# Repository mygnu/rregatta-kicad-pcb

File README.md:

# rregatta-kicad-pcb

Full tutorial at [Building a sailing starter board with Rust (RTIC)](https://gill.net.in/posts/stm32-pcb-sailing-and-rust/)

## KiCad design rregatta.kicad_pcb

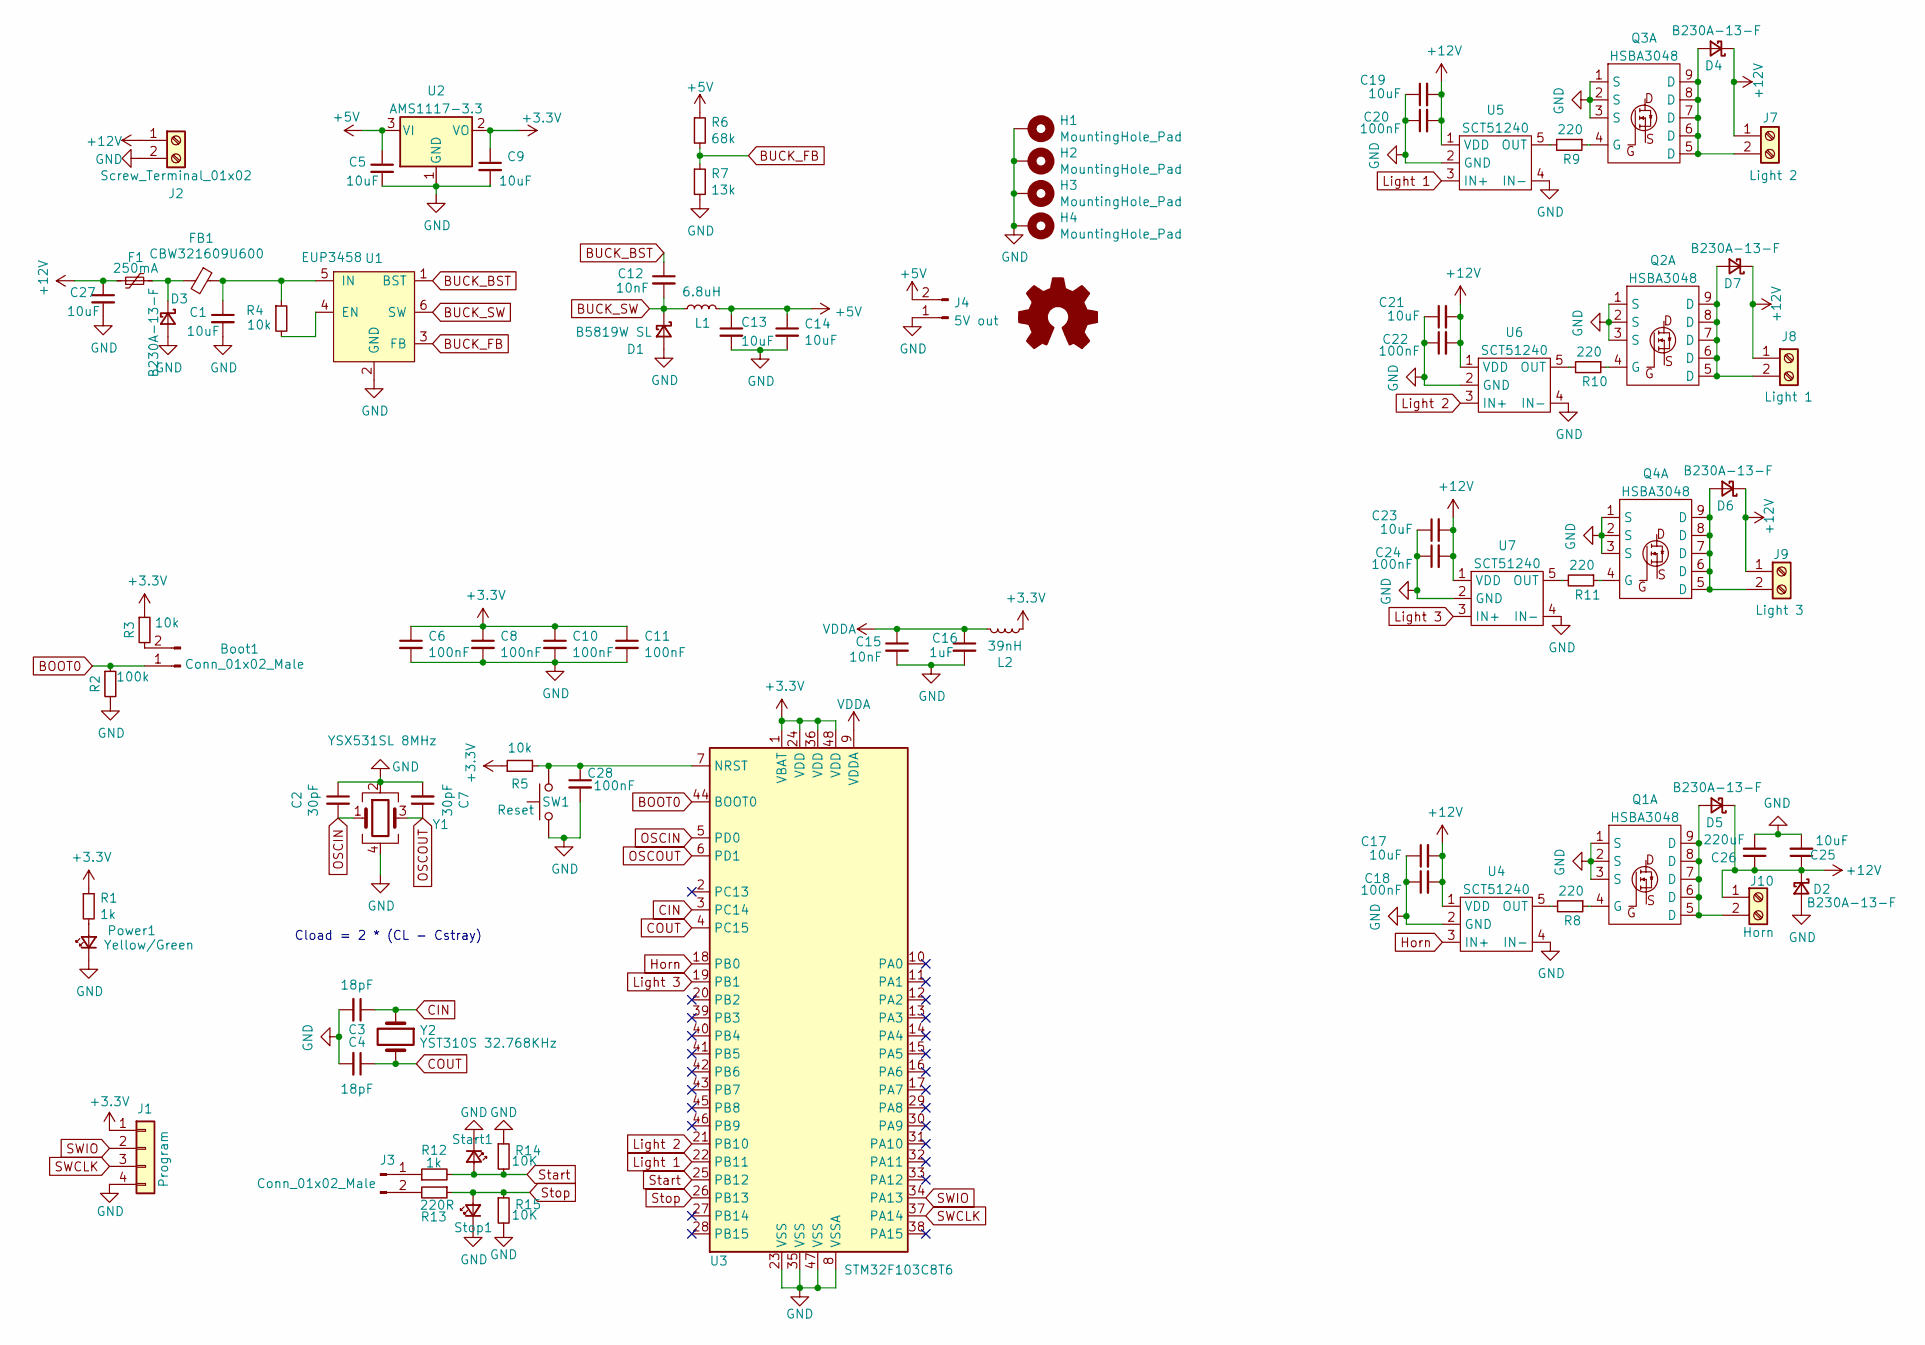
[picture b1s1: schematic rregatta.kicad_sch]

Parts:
Boot1: Conn_01x02_Male; PinHeader_1x02_P2.54mm_Vertical
C1, C5, C9, C13, C14, C17, C19, C21, C23, C25, C27: 10uF; C_0603_1608Metric_Pad1.08x0.95mm_HandSolder
C2, C7: 30pF; C_0603_1608Metric_Pad1.08x0.95mm_HandSolder
C3, C4: 18pF; C_0603_1608Metric_Pad1.08x0.95mm_HandSolder
C6, C8, C10, C11, C18, C20, C22, C24, C28: 100nF; C_0603_1608Metric_Pad1.08x0.95mm_HandSolder
C12, C15: 10nF; C_0603_1608Metric_Pad1.08x0.95mm_HandSolder
C16: 1uF; C_0603_1608Metric_Pad1.08x0.95mm_HandSolder
C26: 220uF; CP_Elec_6.3x7.7
D1: B5819W SL; D_SOD-123
D2, D3, D4, D5, D6, D7: B230A-13-F; D_SMA
F1: 250mA; Fuse_1206_3216Metric_Pad1.42x1.75mm_HandSolder
FB1: CBW321609U600; C_1206_3216Metric_Pad1.33x1.80mm_HandSolder
H1, H2, H3, H4: MountingHole_Pad; MountingHole_3mm_Pad_Via
J1: Program; PinHeader_1x04_P2.54mm_Vertical
J2: Screw_Terminal_01x02; TerminalBlock_bornier-2_P5.08mm
J3: Conn_01x02_Male; PinHeader_1x02_P2.54mm_Vertical
J4: 5V out; PinHeader_1x02_P2.54mm_Vertical
J7: Light 2; TerminalBlock_bornier-2_P5.08mm
J8: Light 1; TerminalBlock_bornier-2_P5.08mm
J9: Light 3; TerminalBlock_bornier-2_P5.08mm
J10: Horn; TerminalBlock_bornier-2_P5.08mm
L1: 6.8uH; L_Bourns-SRN4018
L2: 39nH; L_0805_2012Metric_Pad1.05x1.20mm_HandSolder
LOGO1: Logo_Open_Hardware_Small; OSHW-Logo2_7.3x6mm_SilkScreen
Power1: Yellow/Green; LED_0603_1608Metric_Pad1.05x0.95mm_HandSolder
Q1, Q2, Q3, Q4: HSBA3048; PDFN-8_L5.6-W5.2-P1.27-LS6.1-BL
R1, R12: 1k; R_0603_1608Metric_Pad0.98x0.95mm_HandSolder
R2: 100k; R_0603_1608Metric_Pad0.98x0.95mm_HandSolder
R3, R4, R5: 10k; R_0603_1608Metric_Pad0.98x0.95mm_HandSolder
R6: 68k; R_0603_1608Metric_Pad0.98x0.95mm_HandSolder
R7: 13k; R_0603_1608Metric_Pad0.98x0.95mm_HandSolder
R8, R9, R10, R11: 220; R_0603_1608Metric_Pad0.98x0.95mm_HandSolder
R13: 220R; R_0603_1608Metric_Pad0.98x0.95mm_HandSolder
R14, R15: 10K; R_0603_1608Metric_Pad0.98x0.95mm_HandSolder
SW1: Reset; SW_Push_7x4.5
Start1: LED; LED_0603_1608Metric_Pad1.05x0.95mm_HandSolder
Stop1: LED; LED_0603_1608Metric_Pad1.05x0.95mm_HandSolder
U1: EUP3458; SOT-23-6_Handsoldering
U2: AMS1117-3.3; SOT-223-3_TabPin2
U3: STM32F103C8T6; LQFP-48_7x7mm_P0.5mm
U4, U5, U6, U7: SCT51240; SOT-23-5_HandSoldering
Y1: YSX531SL 8MHz; Crystal_SMD_3225-4Pin_3.2x2.5mm
Y2: YST310S 32.768KHz; Crystal_SMD_3215-2Pin_3.2x1.5mm

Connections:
+3V3: C6.1, C8.1, C9.1, C10.1, C11.1, J1.1, L2.1, R1.1, R3.1, R5.1, U2.2 (VO), U3.1 (VBAT), U3.24 (VDD), U3.36 (VDD), U3.48 (VDD)
+5V: C5.1, C13.1, C14.1, J4.2, L1.2, R6.1, U2.3 (VI)
+12V: C17.2, C18.2, C19.2, C20.2, C21.2, C22.2, C23.2, C24.2, C25.1, C26.1, C27.1, D2.1 (K), D4.1 (K), D5.1 (K), D6.1 (K), D7.1 (K), F1.1, J2.1, J7.1, J8.1, J9.1, J10.1, U4.1 (VDD), U5.1 (VDD), U6.1 (VDD), U7.1 (VDD)
BOOT0: Boot1.1, R2.1, U3.44 (BOOT0)
BUCK_BST: C12.1, U1.1 (BST)
BUCK_FB: R6.2, R7.1, U1.3 (FB)
BUCK_SW: C12.2, D1.1 (K), L1.1, U1.6 (SW)
CIN: C3.1, U3.3 (PC14), Y2.1
COUT: C4.1, U3.4 (PC15), Y2.2
GND: C1.2, C2.1, C3.2, C4.2, C5.2, C6.2, C7.2, C8.2, C9.2, C10.2, C11.2, C13.2, C14.2, C15.2, C16.2, C17.1, C18.1, C19.1, C20.1, C21.1, C22.1, C23.1, C24.1, C25.2, C26.2, C27.2, C28.2, D1.2 (A), D2.2 (A), D3.2 (A), H1.1, H2.1, H3.1, H4.1, J1.4, J2.2, J4.1, Power1.1 (K), Q1.1 (S), Q1.2 (S), Q1.3 (S), Q2.1 (S), Q2.2 (S), Q2.3 (S), Q3.1 (S), Q3.2 (S), Q3.3 (S), Q4.1 (S), Q4.2 (S), Q4.3 (S), R2.2, R7.2, R14.1, R15.2, SW1.1, Start1.1 (K), Stop1.1 (K), U1.2 (GND), U2.1 (GND), U3.8 (VSSA), U3.23 (VSS), U3.35 (VSS), U3.47 (VSS), U4.2 (GND), U4.4 (IN-), U5.2 (GND), U5.4 (IN-), U6.2 (GND), U6.4 (IN-), U7.2 (GND), U7.4 (IN-), Y1.2, Y1.4
Horn: U3.18 (PB0), U4.3 (IN+)
Light 1: U3.22 (PB11), U5.3 (IN+)
Light 2: U3.21 (PB10), U6.3 (IN+)
Light 3: U3.19 (PB1), U7.3 (IN+)
unnamed: Boot1.2, R3.2
unnamed: C1.1, FB1.1, R4.1, U1.5 (IN)
unnamed: C28.1, R5.2, SW1.2, U3.7 (NRST)
unnamed: D3.1 (K), F1.2, FB1.2
unnamed: D4.2 (A), J7.2, Q3.5 (D), Q3.6 (D), Q3.7 (D), Q3.8 (D), Q3.9 (D)
unnamed: D5.2 (A), J10.2, Q1.5 (D), Q1.6 (D), Q1.7 (D), Q1.8 (D), Q1.9 (D)
unnamed: D6.2 (A), J9.2, Q4.5 (D), Q4.6 (D), Q4.7 (D), Q4.8 (D), Q4.9 (D)
unnamed: D7.2 (A), J8.2, Q2.5 (D), Q2.6 (D), Q2.7 (D), Q2.8 (D), Q2.9 (D)
unnamed: J3.1, R12.1
unnamed: J3.2, R13.2
unnamed: Power1.2 (A), R1.2
unnamed: Q1.4 (G), R8.1
unnamed: Q2.4 (G), R10.1
unnamed: Q3.4 (G), R9.1
unnamed: Q4.4 (G), R11.1
unnamed: R4.2, U1.4 (EN)
unnamed: R8.2, U4.5 (OUT)
unnamed: R9.2, U5.5 (OUT)
unnamed: R10.2, U6.5 (OUT)
unnamed: R11.2, U7.5 (OUT)
OSCIN: C2.2, U3.5 (PD0), Y1.1
OSCOUT: C7.1, U3.6 (PD1), Y1.3
SWCLK: J1.3, U3.37 (PA14)
SWIO: J1.2, U3.34 (PA13)
Start: R12.2, R14.2, Start1.2 (A), U3.25 (PB12)
Stop: R13.1, R15.1, Stop1.2 (A), U3.26 (PB13)
VDDA: C15.1, C16.1, L2.2, U3.9 (VDDA)

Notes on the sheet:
Cload = 2 * (CL - Cstray)

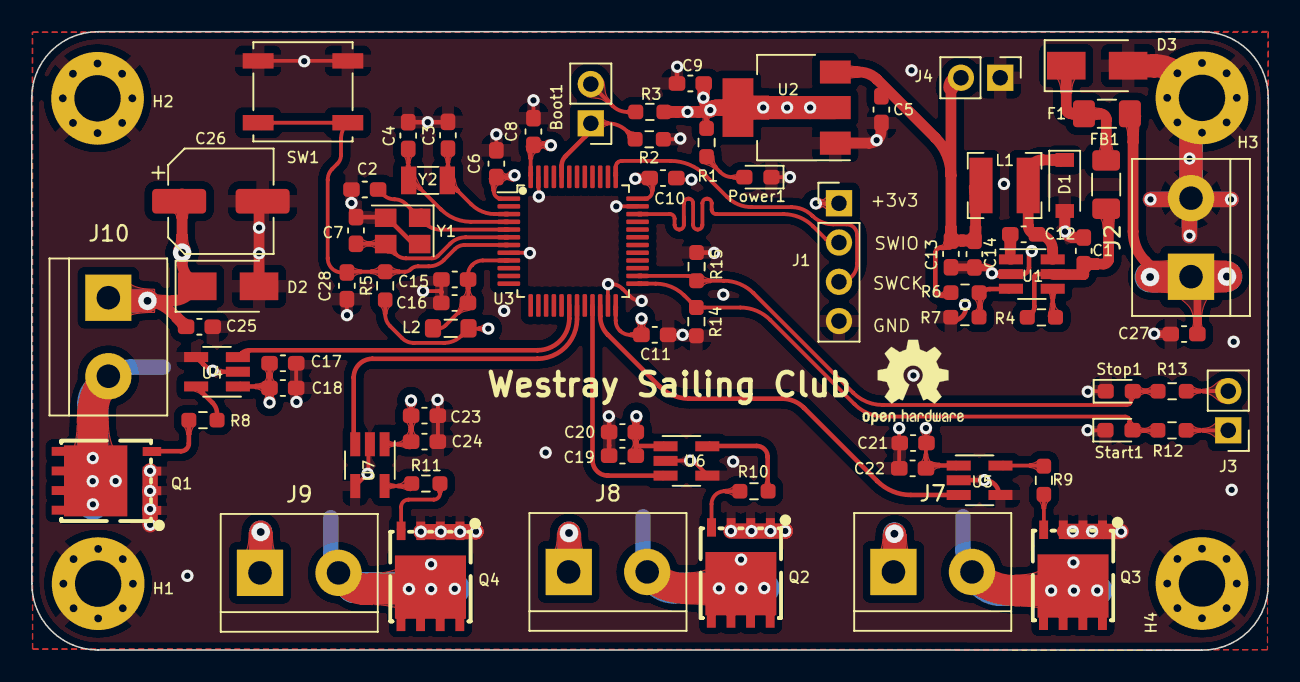
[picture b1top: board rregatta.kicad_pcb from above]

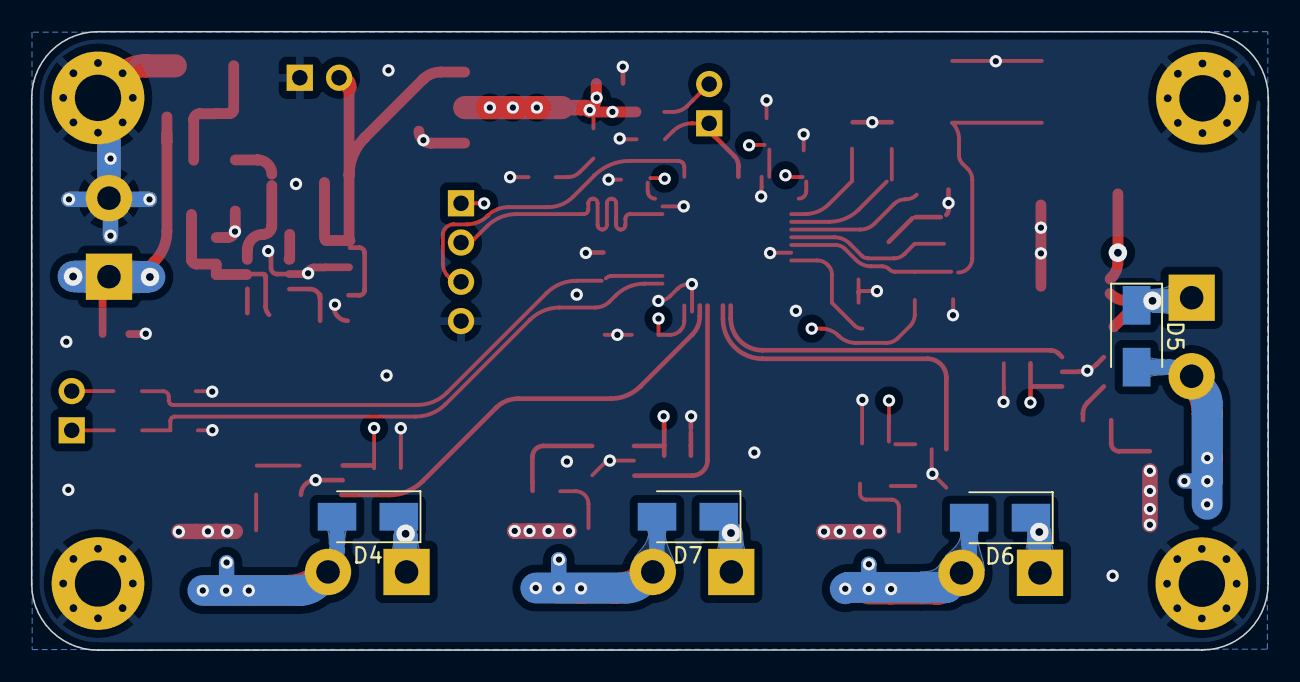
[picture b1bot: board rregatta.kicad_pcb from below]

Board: 4 copper layers, 80.0 x 40.0 mm, 85 parts (4 on the bottom side), 41 nets.

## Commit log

2022-05-29 move to github
2022-05-29 update render
2022-05-29 test url
